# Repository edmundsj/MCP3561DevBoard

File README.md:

# MCP3561 Development Board
Development board for MCP3561 ADC, a <153kSpS
sigma-delta (oversampling) ADC capable of ~108dB SNR.

## Features
- 3.3V on-board reference
- low-noise 3.3V digital and analog supplies
- Powered via single 4V-12V input voltage
- Sampling rate tested up to 10kHz
- BNC input synchronization
- Single-channel SMA analog input
- Based on the Teensy 4.1, micro-USB communication to PC
- Additional digital/analog outputs (used here for motor control)

## Performance Data
Measured with MCLK=10MHz, OSR=256, fs=9.76kHz, Av=1
- Rms voltage noise 9.8uV, PSD=143nV/rtHz, 0.2kHz to fs/2

Measured with MCLK=10MHz, OSR=256, fs=9.76kHz, Av=10
- Rms voltage noise is 13.4uV, PSD=195nV/rtHz, 0.2kHz to fs/2

Fig. 3 and 4 show the same plots with an input signal of 10mVrms (Av=10) at
105Hz.

Fig. 5 and 6 show the same plots with an input signal of 100mVrms (Av=10) at
205Hz. 

## Getting Started
Using this dev board requires you have python installed on your computer, as
well as the Teensyduino IDE. You must then upload the code in ``arduino_code/``
to the Teensy being used for measurement, which I have written to communicate
via the arduino ``Serial()`` interface (USB) using the SCPI language. Feel free
to communicate with it using your own scripts, but I have written a python
implementation which can be found in ``MCP3561.py``
[here](https://github.com/edmundsj/AD7766_Python.git).

## Issues
### Issues in version 1
- [FIXED v2] U3 (TLV opamp) package is incorrect - TSOT353, actual package is SOT23-5.
- 1/f noise of TLV opamp is appreciable when configured for a gain of 10.

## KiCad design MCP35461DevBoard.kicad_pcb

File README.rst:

MCP3561 Development Board
============================

Getting Started
------------------
- NOTE: To run unit tests with a different sampling frequency than 4.8kHz, you need to change the sampling frequency in the unit test suite.
Run:
.. code-block::
	
	python -m unittest discover

This should cause 20 unit tests to be run (1 may be skipped). Two should fail if the EXT_SYNC signal is not receiving a 1kHz pulse train, and 17 should pass.

Issues in version 1
---------------------
- [FIXED v2] U3 (TLV opamp) package is incorrect. TSOT353, actual package SOT23-5.

Test Data

Appendix - Notes
-------------------
- I will try to solder on U3 anyway despite its smaller package. I have a microscope, hopefully that will help :p.
- Got it. Damn that was not trivial, don't know how I would have done it without a microscope.
- All input voltages are as expected, 3.3V except for VOS, which is 0.8V (3.3V/4). With the labeled test points it was SO EASY to do this test. It took a total of like 5 seconds. Now we solder on the teensy and attempt to write software to communicate with the ADC.
- Soldering the ADC on applying flux liberally and a very small amount of solder to the tip was pretty trivial.
- Why is the ADC data 32 bits and not 24? Is it sending a checksum or something? Nope, the checksum is 16 bits. Nope, default length is 24 bits.
- Does this chip have no static write? God that's going to be annoying to deal with.
- I was seeing strange periodic pulses on the Teeny's supply - turns out the thing was not actually connected to ground! I left the pin floating because I didn't have a long-enough header and didn't realize that was where my ground pin was connected.
- We are sending a clock signal on the SPI SCK line, but we are not getting any data back from the ADC. We should verify that the registers we wrote have the correct values.
- The ADC is completely silent when I try to read its registers. They all contain nothing. I suspect the ADC is locked or I am not sending the right command.
- Much better. I forgot to send the address on the SPI bus. Stupid protocol. 
- I have verified that the CONFIG0-3 registers have the correct value. MCLK is going off at 4.69MHz, and pin 7 of the Teensy is being driven. The ADC data is in continuous conversion mode, but all the bits we are getting back are zero.
- When I plugged in the ADC initially today it was reading all zeros - this tells me that I am trying to write the register defaults too fast. I added a 100ms delay on startup prior to writing to try to fix this. This doesn't seem to work. 500ms does seem to work.
- For some reason our beginReadingData() function isn't working, we simply re-read the last ADC value over and over again.
- Our readRegisters() command works, but beginReadingData() does not. What's the difference? We are doing an incremental read in the one case and a static read in the other. Not sure why this would make a difference.
- So the static read is working, but the continuous read is not. It seems like the ADC is not continually generating new data (or updating the output register) until we send the read command. This is fine for now. This is fine for now.
- The master clock of the ADC is running at 4.691MHz, and the data appears to be ready at a frequency of 4.584kHz, which would seem to indicate there is one sample every 1024 clock cycles. According to the datasheet at this clock frequency and an oversampling ratio of 256, the data rate should be 4.581kHz, which is very close to what we see. This means the ADC is working as expected. The interrupt pin is also working well, so we need to implement that.
- Everything is now working, sampling at 4.8kHz. 
- Looks like I can sample at 36.8kHz, but the data is in steps of 180, not steps of 1 anymore. That's obnoxious. For now I'll just stick with a sampling rate of 4.8kHz and characterize the ADC, then switch to a higher sampling rate.
- For now, I have commented out all the motor and synchronization code, but even the identify code is not working. Ported code is now working.
- I will test using a 10MHz clock at the input

Unit Test Debugging
____________________
- I am having some issues getting 300,000 bytes back from the arduino. I suspect this is a time-out error, as we need to wait quite a long time to get back this data. I'm receiving around 40kB, which indicates we only take ~10 measurements. I'm going to try to do this manually.
- The teensy itself can send 100k samples no problem.
- Sure enough, our Measure() method is terminating too early. Fixed it, now it's working up to 100k measurements.
- All motor communication unit tests are now passing, as are all measurement tests. Still failing synchronization tests, which means I will have to solder on the connector. Time to do that.
- Today the measurement frequency is 4.58kHz. This is significantly lower than yesterday, it looks like the internal clock drifts quite a bit. Let's drive the clock using the Teensy to try to get a more reliable sampling rate.
- Synchronization is not currently working. I'm going to let that issue rest for now. The discrepancy is small.

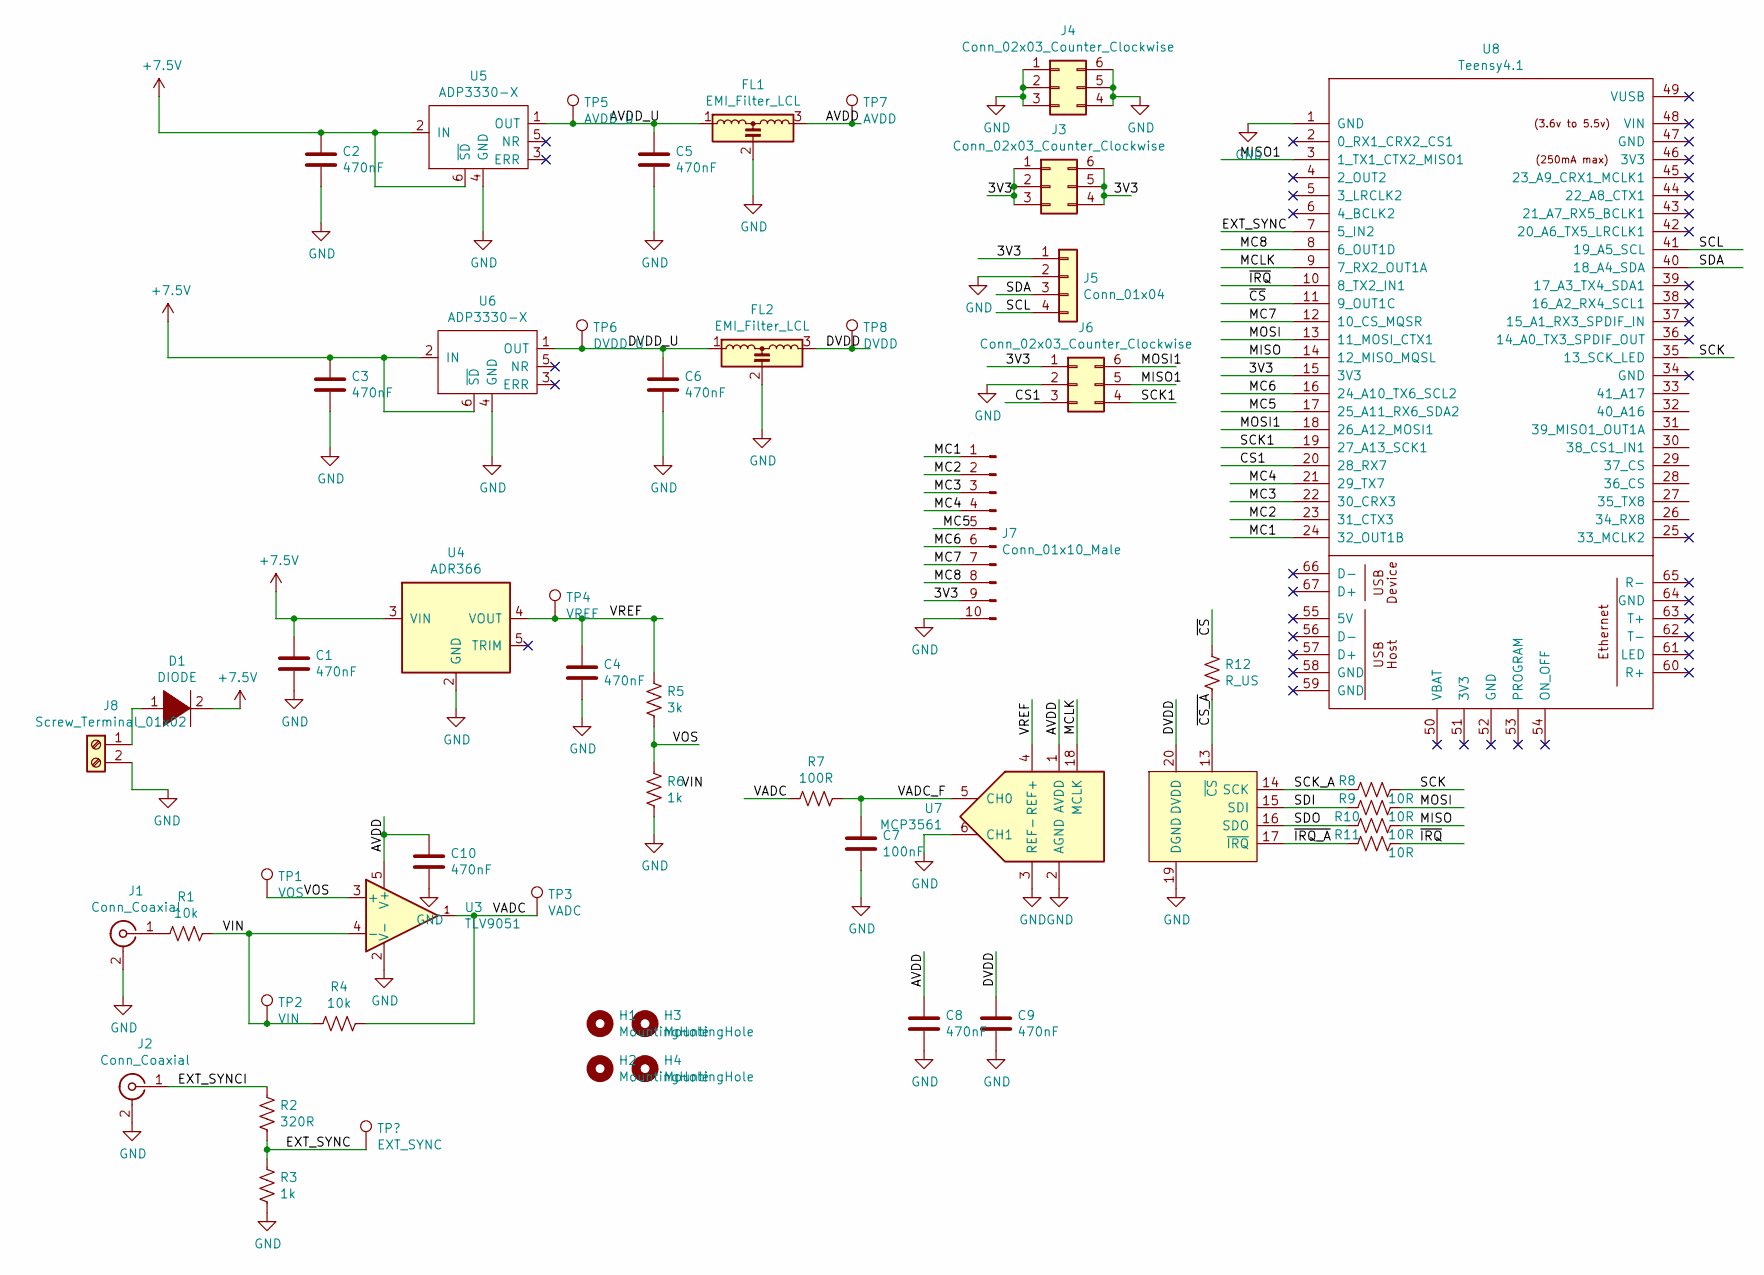
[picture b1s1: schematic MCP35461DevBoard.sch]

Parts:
C1, C2, C3, C4, C5, C6, C8, C9, C10: 470nF; C_0805_2012Metric_Pad1.15x1.40mm_HandSolder
C7: 100nF; C_0805_2012Metric_Pad1.15x1.40mm_HandSolder
D1: DIODE; D_SMA-SMB_Universal_Handsoldering
FL1, FL2: EMI_Filter_LCL; 0805_3TERM
H1, H2, H3, H4: MountingHole; m3_mounting_hole
J1: Conn_Coaxial; CON-SMA-EDGE-S
J2: Conn_Coaxial; BNC_JACK_RA
J3, J4, J6: Conn_02x03_Counter_Clockwise; PinHeader_2x03_P2.54mm_Vertical
J5: Conn_01x04; PinHeader_1x04_P2.54mm_Vertical
J7: Conn_01x10_Male; PinHeader_1x10_P2.54mm_Vertical
J8: Screw_Terminal_01x02; TerminalBlock_Altech_AK300-2_P5.00mm
R1, R4: 10k; R_0805_2012Metric_Pad1.15x1.40mm_HandSolder
R2: 320R; R_0805_2012Metric_Pad1.15x1.40mm_HandSolder
R3, R6: 1k; R_0805_2012Metric_Pad1.15x1.40mm_HandSolder
R5: 3k; R_0805_2012Metric_Pad1.15x1.40mm_HandSolder
R7: 100R; R_0805_2012Metric_Pad1.15x1.40mm_HandSolder
R8, R9, R10, R11: 10R; R_0805_2012Metric_Pad1.15x1.40mm_HandSolder
R12: R_US; R_0805_2012Metric_Pad1.15x1.40mm_HandSolder
TP1: VOS; TestPoint_Keystone_5000-5004_Miniature
TP2: VIN; TestPoint_Keystone_5000-5004_Miniature
TP3: VADC; TestPoint_Keystone_5000-5004_Miniature
TP4: VREF; TestPoint_Keystone_5000-5004_Miniature
TP5: AVDD_U; TestPoint_Keystone_5000-5004_Miniature
TP6: DVDD_U; TestPoint_Keystone_5000-5004_Miniature
TP7: AVDD; TestPoint_Keystone_5000-5004_Miniature
TP8: DVDD; TestPoint_Keystone_5000-5004_Miniature
U3: TLV9051; SOT-353_SC-70-5
U4: ADR366; TSOT-23-5_HandSoldering
U5, U6: ADP3330-X; SOT-23-6_Handsoldering
U7: MCP3561; TSSOP-20_4.4x6.5mm_P0.65mm
U8: Teensy4.1; Teensy41

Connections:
+7.5V: C1.1, C2.1, C3.1, D1.2 (A), U4.3 (VIN), U5.2 (IN), U5.6 (~SD), U6.2 (IN), U6.6 (~SD)
/3V3: J3.1, J3.2, J3.3, J3.4, J3.5, J3.6, J5.1, J6.1, J7.9, U8.15 (3V3)
/AVDD: C8.1, C10.1, FL1.3, TP7.1, U3.5 (V+), U7.1 (AVDD)
/AVDD_U: C5.1, FL1.1, TP5.1, U5.1 (OUT)
/CS1: J6.3, U8.20 (28_RX7)
/DVDD: C9.1, FL2.3, TP8.1, U7.20 (DVDD)
/DVDD_U: C6.1, FL2.1, TP6.1, U6.1 (OUT)
/EXT_SYNC: R2.2, R3.1, U8.7 (5_IN2); also elsewhere on the board
/EXT_SYNCI: J2.1 (In), R2.1
/MC1: J7.1, U8.24 (32_OUT1B)
/MC2: J7.2, U8.23 (31_CTX3)
/MC3: J7.3, U8.22 (30_CRX3)
/MC4: J7.4, U8.21 (29_TX7)
/MC5: J7.5, U8.17 (25_A11_RX6_SDA2)
/MC6: J7.6, U8.16 (24_A10_TX6_SCL2)
/MC7: J7.7, U8.12 (10_CS_MQSR)
/MC8: J7.8, U8.8 (6_OUT1D)
/MCLK: U7.18 (MCLK), U8.9 (7_RX2_OUT1A)
/MISO: R10.1, U8.14 (12_MISO_MQSL)
/MISO1: J6.5, U8.3 (1_TX1_CTX2_MISO1)
/MOSI: R9.1, U8.13 (11_MOSI_CTX1)
/MOSI1: J6.6, U8.18 (26_A12_MOSI1)
/SCK: R8.1, U8.35 (13_SCK_LED)
/SCK1: J6.4, U8.19 (27_A13_SCK1)
/SCK_A: R8.2, U7.14 (SCK)
/SCL: J5.4, U8.41 (19_A5_SCL)
/SDA: J5.3, U8.40 (18_A4_SDA)
/SDI: R9.2, U7.15 (SDI)
/SDO: R10.2, U7.16 (SDO)
/VADC: R4.1, R7.2, TP3.1, U3.1 (OUT)
/VADC_F: C7.1, R7.1, U7.5 (CH0)
/VIN: R1.1, R4.2, TP2.1, U3.4 (-)
/VOS: R5.2, R6.1, TP1.1, U3.3 (+)
/VREF: C4.1, R5.1, TP4.1, U4.4 (VOUT), U7.4 (REF+)
/~CS: R12.1, U8.11 (9_OUT1C)
/~CS_A: R12.2, U7.13 (~CS)
/~IRQ: R11.1, U8.10 (8_TX2_IN1)
/~IRQ_A: R11.2, U7.17 (~IRQ)
GND: C1.2, C2.2, C3.2, C4.2, C5.2, C6.2, C7.2, C8.2, C9.2, C10.2, FL1.2, FL2.2, J1.2 (Ext), J2.2 (Ext), J4.1, J4.2, J4.3, J4.4, J4.5, J4.6, J5.2, J6.2, J7.10, J8.2, R3.2, R6.2, U3.2 (V-), U4.2 (GND), U5.4 (GND), U6.4 (GND), U7.2 (AGND), U7.3 (REF-), U7.6 (CH1), U7.19 (DGND), U8.1 (GND)
unnamed: D1.1 (K), J8.1
unnamed: J1.1 (In), R1.2

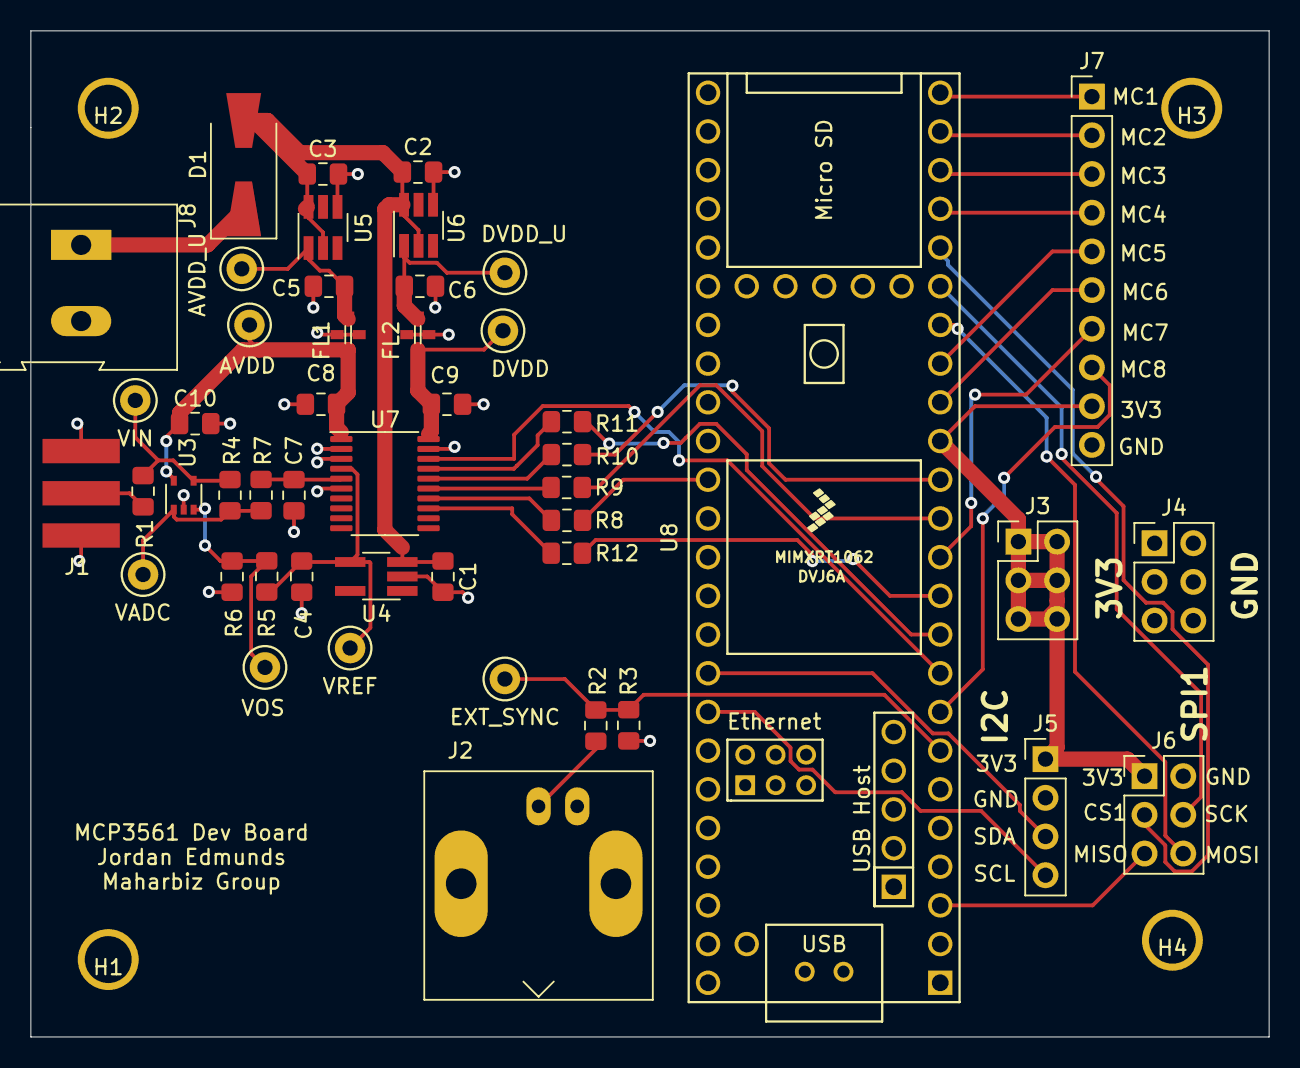
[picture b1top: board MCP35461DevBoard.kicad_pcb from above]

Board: 2 copper layers, 81.3 x 66.0 mm, 52 parts (0 on the bottom side), 41 nets.

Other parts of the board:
TP9: EXT_SYNC; TestPoint_Keystone_5000-5004_Miniature

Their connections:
/EXT_SYNC: TP9.1; also elsewhere on the board

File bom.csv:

Part Name,,Source, Catalog Number,Link, Quantity
    U8,Teensy4.1,Digikey,,,1
    U7,MCP3561,Digikey,MCP3561RT-E/ST,https://www.digikey.com/en/products/detail/microchip-technol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,1
">  U5, U6",ADP3330-3.3,Digikey,ADP3330ARTZ3.3-RL7CT-ND,https://www.digikey.com/en/products/detail/analog-devices-in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,2
    U4,ADR366,Digikey,ADR366AUJZ-REEL7,https://www.digikey.com/en/products/detail/analog-devices-in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,1
    U3,TLV9051,Digikey,TLV9051IDBVR,https://www.digikey.com/en/products/detail/texas-instruments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,1
>  R8-R12,10R,Digikey,,,4
">  R3, R6",1k,Digikey,,,2
    R7,100R,Digikey,,,1
    R5,3k,Digikey,,,1
">  R1, R4",10k,Digikey,,,2
    R2,320R,Digikey,,,1
    J8,Screw_Terminal_01x02,Digikey,,,1
    J5,Conn_01x04,Digikey,,,1
    J7,Conn_01x10_Male,Digikey,,,1
">  J3, J4, J6",Conn_02x03_Counter_Clockwise,Digikey,,,3
    J1,Conn_Coaxial,Digikey,,,1
    J2,Conn_Coaxial,Digikey,,,1
>  H1-H4,MountingHole,Digikey,,,4
">  FL1, FL2",EMI_Filter_LCL,Digikey,,,2
    D1,DIODE,Digikey,,,1
    C7,100nF,Digikey,,,1
">  C1-C6, C8-C10",470nF,Digikey,,,9

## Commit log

2021-01-14 first version of MCP3561 development board, contains socket for teensy, test points, power via screw terminals, a voltage reference, a unity-gain preamplifier
2021-01-14 fixed power plane so that it contains voltage reference
2021-01-14 added bill of materials with full component list and partial cart
2021-01-19 updated schematic and backup
2021-01-27 added basic arduino code for SCPI communication over serial with arduino. Tested and works at 4.8kHz, there is some funky stuff going on at 38kHz, the ADC has a lower resolution and I'm not sure how 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
2021-01-28 added stepper motor, fixed code on MCP so that all unit tests are passing
2021-03-02 switched README.rst to README.md for better github compatibility. Added updates to teensy code, and added a figure for adc noise
2021-03-05 removed old figures, data. Added figures to README
2021-03-05 added raw data and figures for grounded input, 10mVrms input, and 100mVrms input
2021-03-05 added personal notes from debugging the PCB
2021-03-05 removed them from README
2021-03-05 updated README with basic getting started
2021-03-08 updated README, added additional figures, PCB photos
2021-03-12 added new data, figures for MCP dev board, varying frequency and voltage
2021-03-23 added updated data, plots
